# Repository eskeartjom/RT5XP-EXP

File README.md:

# RT5XP-EXP
A input expander for the RetroTINK 5X-Pro

---
## Introduction
The RT5XP-EXP is a purpose build device to extend the input capabilities of the RetroTINK 5X-Pro.

### Input
The Following video signals are supported:

- SCART (RGBS, RGsB, YPbPr)
- Component (YPbPr, RGsB)
- VGA (RGBHV, RGBS, RGsB, YPbPr)

Audio signals can be input as RCA, 3.5mm Jack or SCART and can be selected independently of the video signal.

The sync on scart and component inputs need to be attenuated 75 Ohm signals.
Scart also supports a attenuated CSync signal as the sync input.

The VGA input only supports TTL signals on the sync pins. When using RGsB/YPbPr these need attenuated correctly (which they should be in the first place). VGA also supports TTL CSync on pin 13.

**Input Resolution***: 240p - 1080i

Switching between resolutions is seamless.

### Output

The RT5XP-EXP outputs the signal in RGBS format out of the left scart connector. This signal should be safe to plug into any scart device. The sync signal is a attenuated csync signal.

**Output Resolution***: 240p - 1080i

*Tested on a RetroTINK 5X-Pro and a OSSC

### Display
The big area on the top left shows the line count* of the current input.
The area on the right shows the measured* horizontal and vertical sync signal.
At the bottom the display shows the currenty used and video and audio input.

*The values may not be 100% accurate but close enough.

### Buttons
- P: Cycles thought presets.
- V: Cycles thought different video inputs.
- F: Cycles thought different formats of the current video input.
- A: Cycles thought different audio inputs.

Holding the P button opens a menu. This menu is still WIP.

---
## Hardware
The hardware consists of following things:

- [Main PCB](./Hardware/MainPCB)
- [Display bracked PCB](./Hardware/DisplayPCB)
- [Case](./Hardware/Case)
- [(Optional) SCART PCB](./Hardware/InterconnectPCB)
- [Display](https://www.adafruit.com/product/5394)

---
## Firmware
NOTE: Is still WIP but usable for the basics
- [Firmware](./Firmware)

The firmware is based on a ATmega4809.
I used the Arduino IDE with following libraries:
- [MegaCoreX](https://github.com/MCUdude/MegaCoreX)
- [Adafruit_ST7789](https://github.com/adafruit/Adafruit-ST7735-Library)
- [Adafruit_GFX](https://learn.adafruit.com/adafruit-gfx-graphics-library/overview)

The microcontroller can be flashed via the usb connection.

---
## Misc
Technically the RT5XP-EXP should be support 1080p resolution but i could not test it.

---
## Known issues
On sharp edges there is a purple "color bending". In game this isn't that noticable or might not be noticed at all.

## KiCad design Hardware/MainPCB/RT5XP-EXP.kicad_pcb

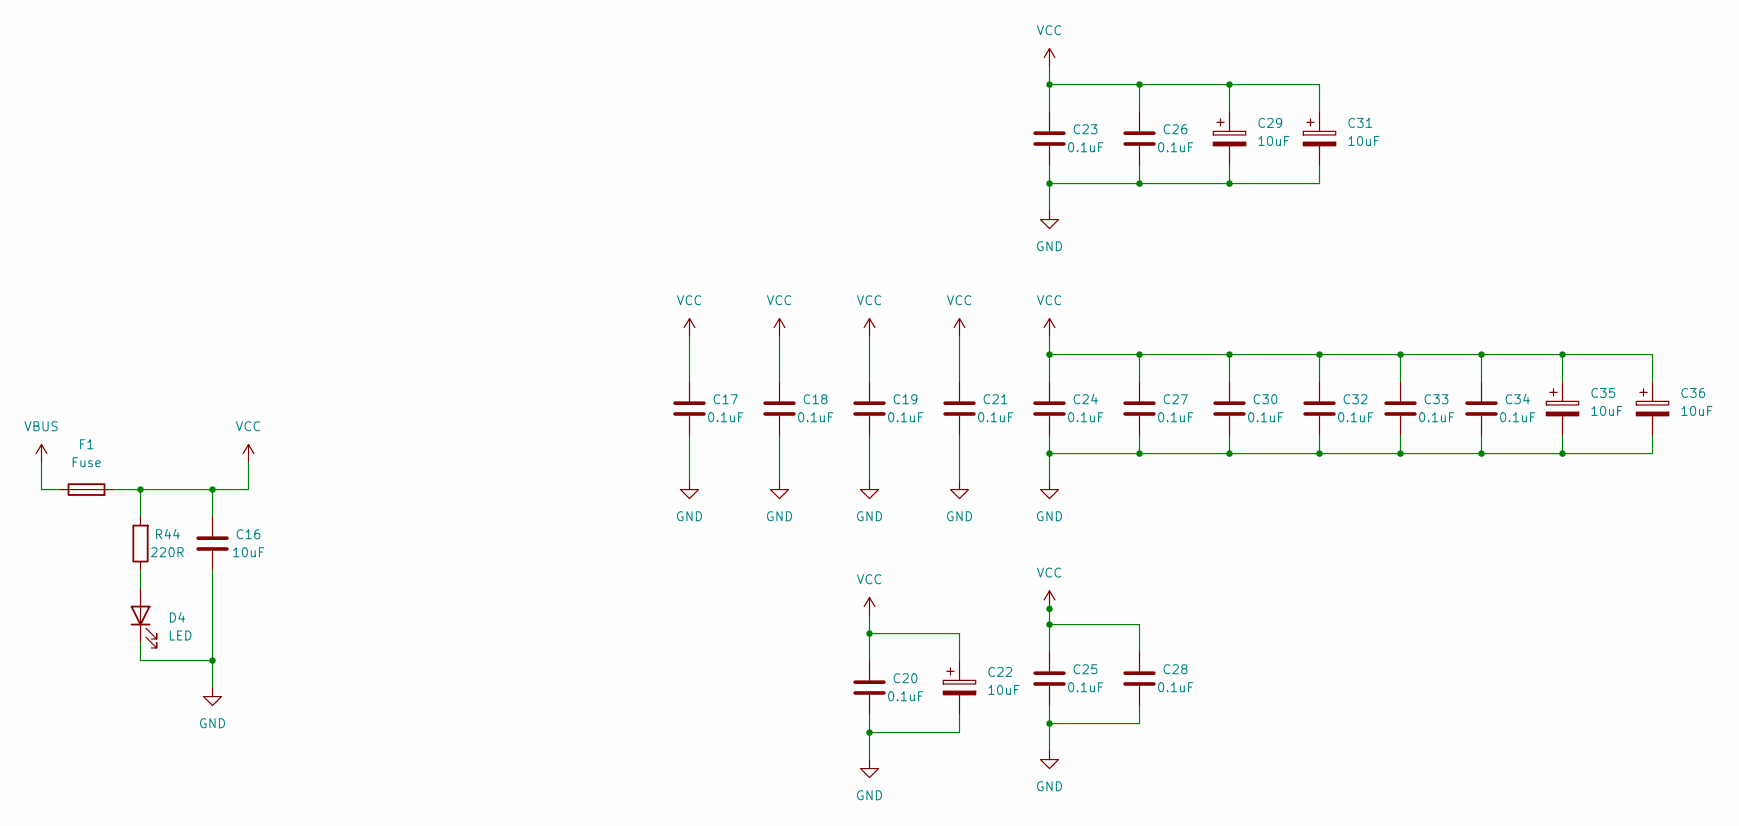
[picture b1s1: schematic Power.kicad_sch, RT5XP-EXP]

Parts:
C16: 10uF; C_0805_2012Metric
C17, C18, C19, C20, C21, C23, C24, C25, C26, C27, C28, C30, C32, C33, C34: 0.1uF; C_0603_1608Metric
C22, C29, C31, C35, C36: 10uF; C_0603_1608Metric
D4: LED; LED_0603_1608Metric
F1: Fuse; Fuse_1210_3225Metric
R44: 220R; R_0603

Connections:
GND: C16.1, C17.1, C18.1, C19.1, C20.1, C21.1, C22.2, C23.1, C24.1, C25.1, C26.1, C27.1, C28.1, C29.2, C30.1, C31.2, C32.1, C33.1, C34.1, C35.2, C36.2, D4.1 (K); also elsewhere on the board
unnamed: D4.2 (A), R44.1
VBUS: F1.1; also elsewhere on the board
VCC: C16.2, C17.2, C18.2, C19.2, C20.2, C21.2, C22.1, C23.2, C24.2, C25.2, C26.2, C27.2, C28.2, C29.1, C30.2, C31.1, C32.2, C33.2, C34.2, C35.1, C36.1, F1.2, R44.2; also elsewhere on the board

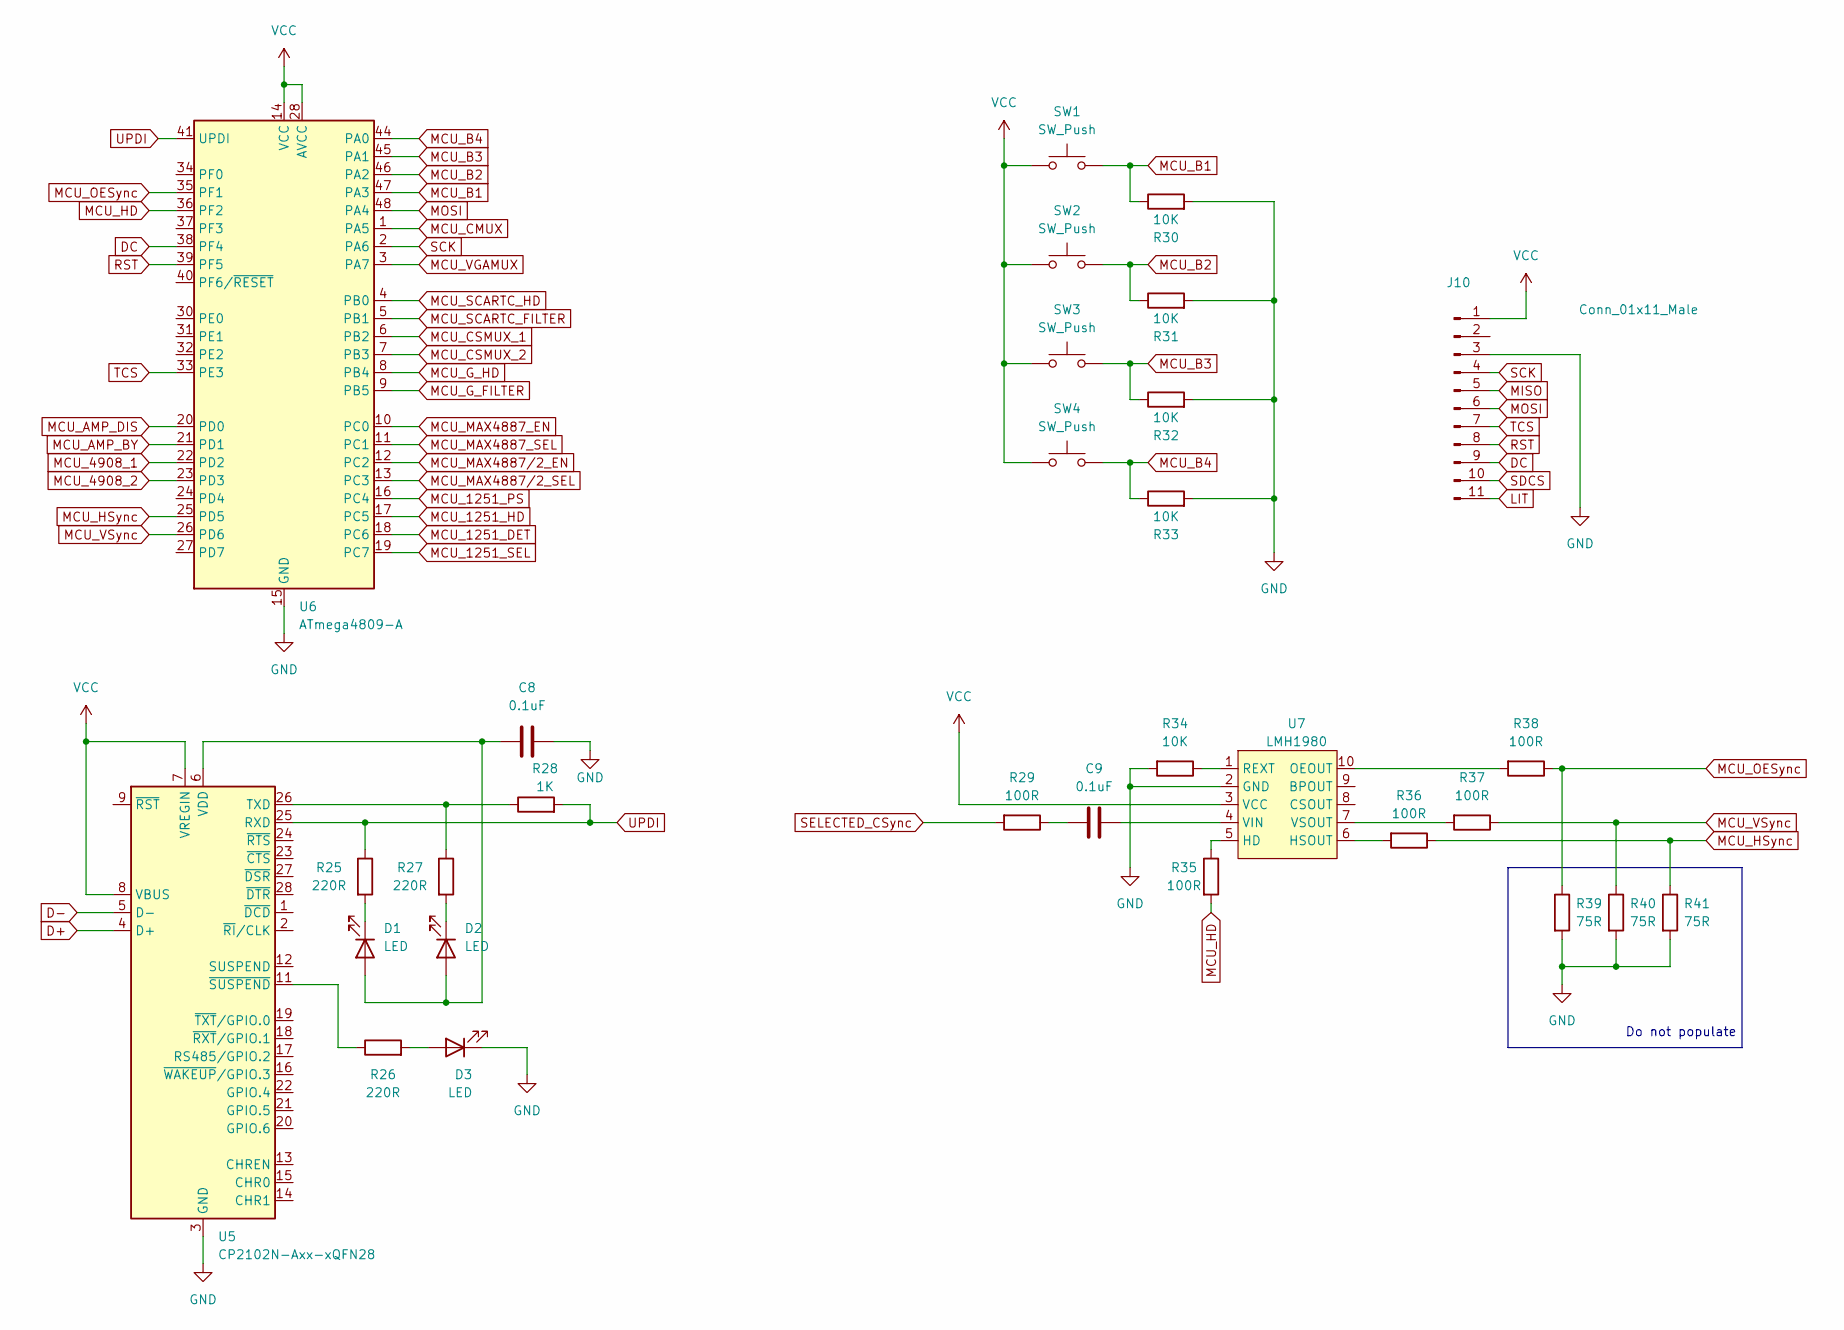
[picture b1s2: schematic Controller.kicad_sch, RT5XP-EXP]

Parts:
C8, C9: 0.1uF; C_0603_1608Metric
D1, D2, D3: LED; LED_0603_1608Metric
J10: Conn_01x11_Male; PinHeader_1x11_P2.54mm_Horizontal
R25, R26, R27: 220R; R_0603
R28: 1K; R_0603
R29, R35, R36, R37, R38: 100R; R_0603
R30, R31, R32, R33, R34: 10K; R_0603
R39, R40, R41: 75R; R_0603
SW1, SW2, SW3, SW4: SW_Push; SW_Tactile_SPST_Angled_PTS645Vx83-2LFS
U5: CP2102N-Axx-xQFN28; QFN-28-1EP_5x5mm_P0.5mm_EP3.35x3.35mm
U6: ATmega4809-A; TQFP-48_7x7mm_P0.5mm
U7: LMH1980; VSSOP-10_3x3mm_P0.5mm

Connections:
D+: U5.4 (D+); also elsewhere on the board
D-: U5.5 (D-); also elsewhere on the board
DC: J10.9, U6.38 (PF4)
GND: C8.1, D3.1 (K), J10.3, R30.2, R31.2, R32.2, R33.2, R34.2, R39.2, R40.2, R41.2, U5.3 (GND), U5.29 (GND), U6.15 (GND), U6.29 (GND), U6.43 (GND), U7.2 (GND); also elsewhere on the board
LIT: J10.11
MCU_1251_DET: U6.18 (PC6); also elsewhere on the board
MCU_1251_HD: U6.17 (PC5); also elsewhere on the board
MCU_1251_PS: U6.16 (PC4); also elsewhere on the board
MCU_1251_SEL: U6.19 (PC7); also elsewhere on the board
MCU_4908_1: U6.22 (PD2); also elsewhere on the board
MCU_4908_2: U6.23 (PD3); also elsewhere on the board
MCU_AMP_BY: U6.21 (PD1); also elsewhere on the board
MCU_AMP_DIS: U6.20 (PD0); also elsewhere on the board
MCU_B1: R30.1, SW1.2, U6.47 (PA3)
MCU_B2: R31.1, SW2.2, U6.46 (PA2)
MCU_B3: R32.1, SW3.2, U6.45 (PA1)
MCU_B4: R33.1, SW4.2, U6.44 (PA0)
MCU_CMUX: U6.1 (PA5); also elsewhere on the board
MCU_CSMUX_1: U6.6 (PB2); also elsewhere on the board
MCU_CSMUX_2: U6.7 (PB3); also elsewhere on the board
MCU_G_FILTER: U6.9 (PB5); also elsewhere on the board
MCU_G_HD: U6.8 (PB4); also elsewhere on the board
MCU_HD: R35.2, U6.36 (PF2)
MCU_HSync: R36.1, R41.1, U6.25 (PD5)
MCU_MAX4887_EN: U6.10 (PC0); also elsewhere on the board
MCU_MAX4887_SEL: U6.11 (PC1); also elsewhere on the board
MCU_MAX4887/2_EN: U6.12 (PC2); also elsewhere on the board
MCU_MAX4887/2_SEL: U6.13 (PC3); also elsewhere on the board
MCU_OESync: R38.1, R39.1, U6.35 (PF1)
MCU_SCARTC_FILTER: U6.5 (PB1); also elsewhere on the board
MCU_SCARTC_HD: U6.4 (PB0); also elsewhere on the board
MCU_VGAMUX: U6.3 (PA7); also elsewhere on the board
MCU_VSync: R37.1, R40.1, U6.26 (PD6)
MISO: J10.5
MOSI: J10.6, U6.48 (PA4)
unnamed: C8.2, D1.2 (A), D2.2 (A), U5.6 (VDD)
unnamed: C9.1, R29.1
unnamed: C9.2, U7.4 (VIN)
unnamed: D1.1 (K), R25.2
unnamed: D2.1 (K), R27.2
unnamed: D3.2 (A), R26.2
unnamed: R26.1, U5.11 (~SUSPEND)
unnamed: R27.1, R28.1, U5.26 (TXD)
unnamed: R34.1, U7.1 (REXT)
unnamed: R35.1, U7.5 (HD)
unnamed: R36.2, U7.6 (HSOUT)
unnamed: R37.2, U7.7 (VSOUT)
unnamed: R38.2, U7.10 (OEOUT)
RST: J10.8, U6.39 (PF5)
SCK: J10.4, U6.2 (PA6)
SDCS: J10.10
SELECTED_CSync: R29.2; also elsewhere on the board
TCS: J10.7, U6.33 (PE3)
UPDI: R25.1, R28.2, U5.25 (RXD), U6.41 (UPDI)
VCC: J10.1, SW1.1, SW2.1, SW3.1, SW4.1, U5.7 (VREGIN), U5.8 (VBUS), U6.14 (VCC), U6.28 (AVCC), U6.42 (VCC), U7.3 (VCC); also elsewhere on the board

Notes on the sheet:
Do not populate

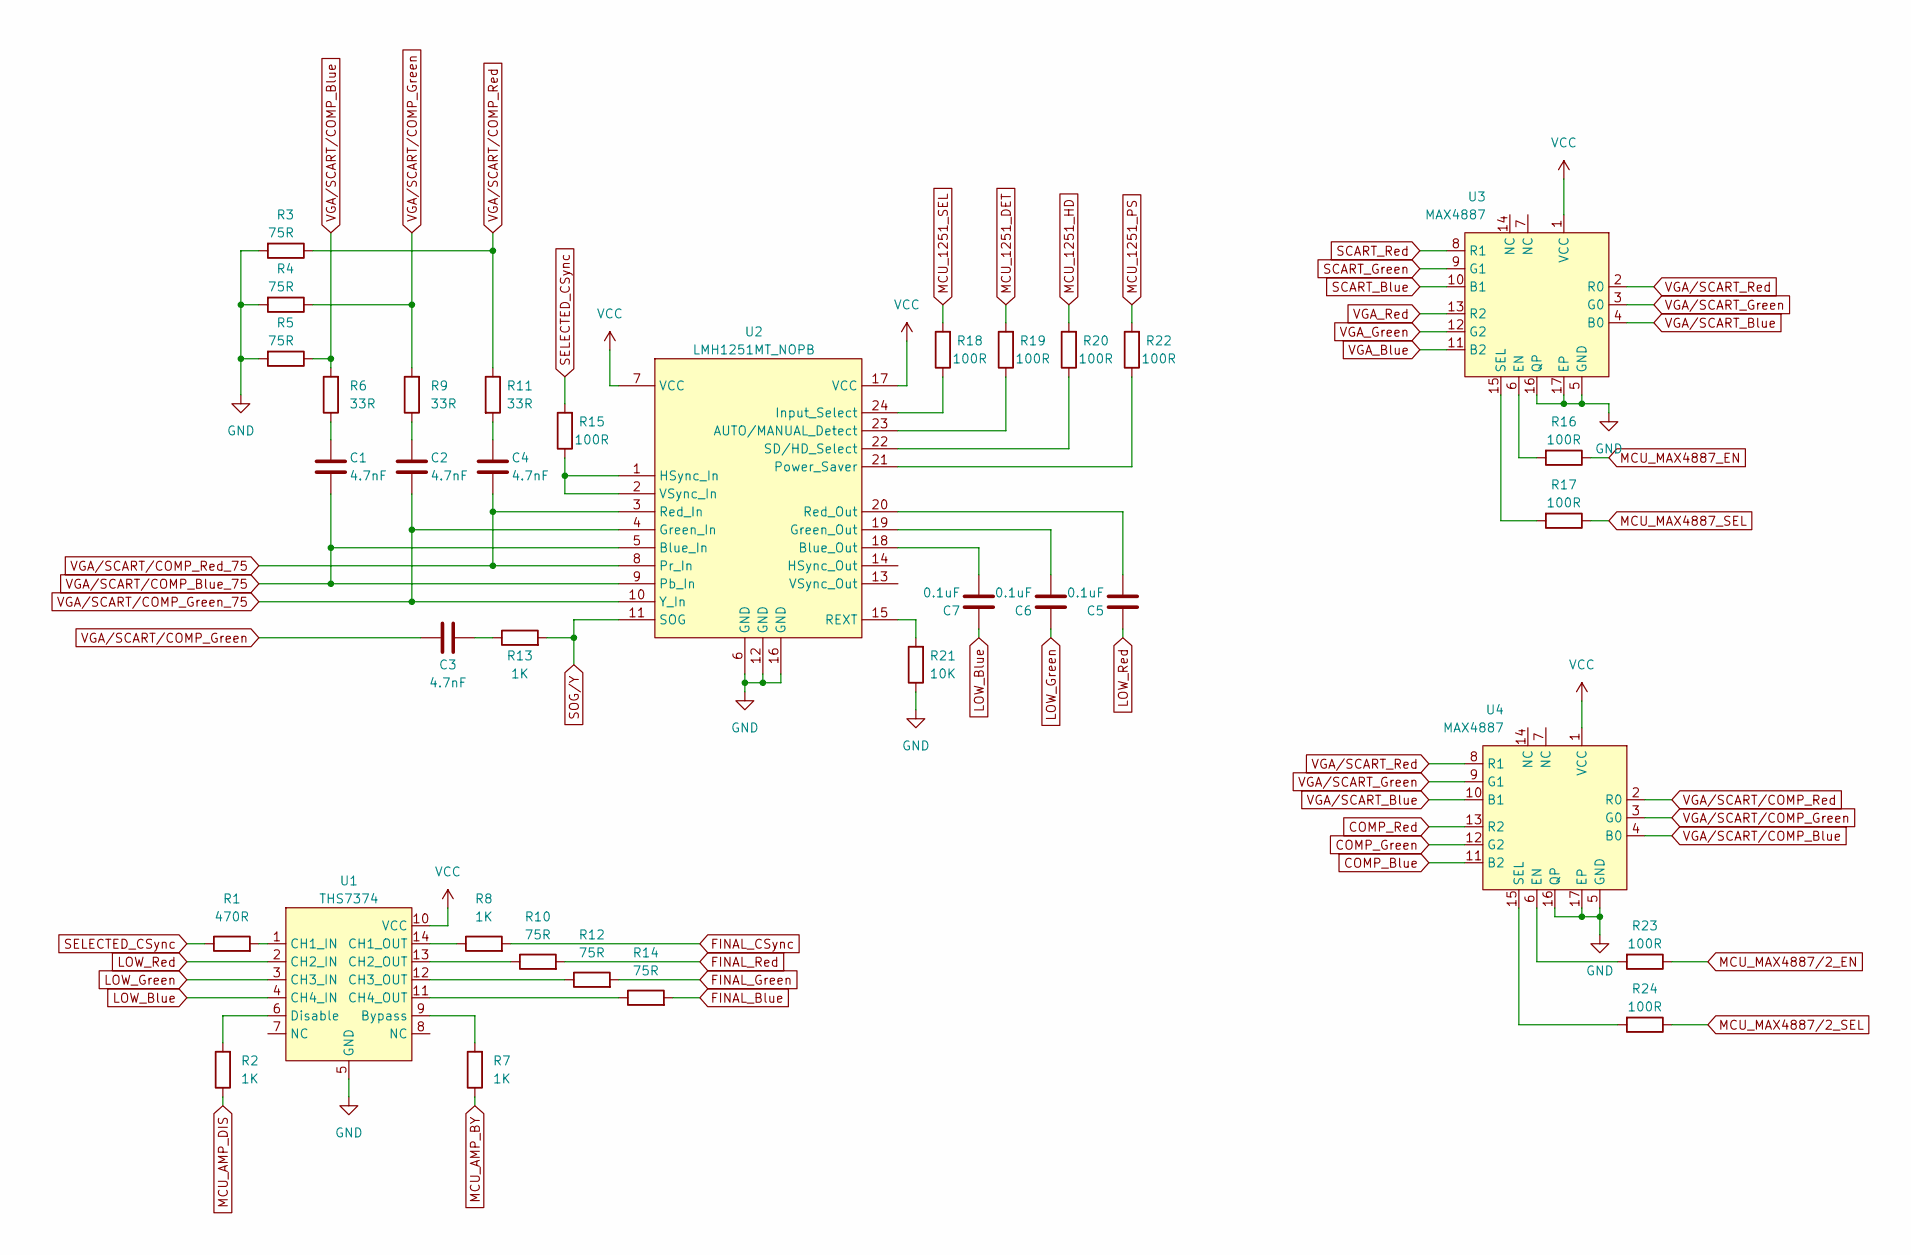
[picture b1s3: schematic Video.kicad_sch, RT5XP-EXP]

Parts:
C1, C2, C3, C4: 4.7nF; C_0603_1608Metric
C5, C6, C7: 0.1uF; C_0603_1608Metric
R1: 470R; R_0603
R2, R7, R8, R13: 1K; R_0603
R3, R4, R5, R10, R12, R14: 75R; R_0603
R6, R9, R11: 33R; R_0603
R15, R16, R17, R18, R19, R20, R22, R23, R24: 100R; R_0603
R21: 10K; R_0603
U1: THS7374; TSSOP-14_4.4x5mm_P0.65mm
U2: LMH1251MT_NOPB; TSSOP-24_4.4x7.8mm_P0.65mm
U3, U4: MAX4887; TQFN-16-1EP_3x3mm_P0.5mm_EP1.23x1.23mm

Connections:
COMP_Blue: U4.11 (B2); also elsewhere on the board
COMP_Green: U4.12 (G2); also elsewhere on the board
COMP_Red: U4.13 (R2); also elsewhere on the board
FINAL_Blue: R14.2; also elsewhere on the board
FINAL_CSync: R8.2; also elsewhere on the board
FINAL_Green: R12.2; also elsewhere on the board
FINAL_Red: R10.2; also elsewhere on the board
GND: R3.2, R4.2, R5.2, R21.1, U1.5 (GND), U2.6 (GND), U2.12 (GND), U2.16 (GND), U3.5 (GND), U3.16 (QP), U3.17 (EP), U4.5 (GND), U4.16 (QP), U4.17 (EP); also elsewhere on the board
LOW_Blue: C7.2, U1.4 (CH4_IN)
LOW_Green: C6.2, U1.3 (CH3_IN)
LOW_Red: C5.2, U1.2 (CH2_IN)
MCU_1251_DET: R19.2; also elsewhere on the board
MCU_1251_HD: R20.2; also elsewhere on the board
MCU_1251_PS: R22.2; also elsewhere on the board
MCU_1251_SEL: R18.2; also elsewhere on the board
MCU_AMP_BY: R7.1; also elsewhere on the board
MCU_AMP_DIS: R2.1; also elsewhere on the board
MCU_MAX4887_EN: R16.1; also elsewhere on the board
MCU_MAX4887_SEL: R17.1; also elsewhere on the board
MCU_MAX4887/2_EN: R23.1; also elsewhere on the board
MCU_MAX4887/2_SEL: R24.1; also elsewhere on the board
unnamed: C1.2, R6.1
unnamed: C2.2, R9.1
unnamed: C3.2, R13.1
unnamed: C4.2, R11.2
unnamed: C5.1, U2.20 (Red_Out)
unnamed: C6.1, U2.19 (Green_Out)
unnamed: C7.1, U2.18 (Blue_Out)
unnamed: R1.2, U1.1 (CH1_IN)
unnamed: R2.2, U1.6 (Disable)
unnamed: R7.2, U1.9 (Bypass)
unnamed: R8.1, U1.14 (CH1_OUT)
unnamed: R10.1, U1.13 (CH2_OUT)
unnamed: R12.1, U1.12 (CH3_OUT)
unnamed: R14.1, U1.11 (CH4_OUT)
unnamed: R15.1, U2.1 (HSync_In), U2.2 (VSync_In)
unnamed: R16.2, U3.6 (EN)
unnamed: R17.2, U3.15 (SEL)
unnamed: R18.1, U2.24 (Input_Select)
unnamed: R19.1, U2.23 (AUTO/MANUAL_Detect)
unnamed: R20.1, U2.22 (SD/HD_Select)
unnamed: R21.2, U2.15 (REXT)
unnamed: R22.1, U2.21 (Power_Saver)
unnamed: R23.2, U4.6 (EN)
unnamed: R24.2, U4.15 (SEL)
SCART_Blue: U3.10 (B1); also elsewhere on the board
SCART_Green: U3.9 (G1); also elsewhere on the board
SCART_Red: U3.8 (R1); also elsewhere on the board
SELECTED_CSync: R1.1, R15.2; also elsewhere on the board
SOG/Y: R13.2, U2.11 (SOG); also elsewhere on the board
VCC: U1.10 (VCC), U2.7 (VCC), U2.17 (VCC), U3.1 (VCC), U4.1 (VCC); also elsewhere on the board
VGA_Blue: U3.11 (B2); also elsewhere on the board
VGA_Green: U3.12 (G2); also elsewhere on the board
VGA_Red: U3.13 (R2); also elsewhere on the board
VGA/SCART_Blue: U3.4 (B0), U4.10 (B1)
VGA/SCART_Green: U3.3 (G0), U4.9 (G1)
VGA/SCART_Red: U3.2 (R0), U4.8 (R1)
VGA/SCART/COMP_Blue: R5.1, R6.2, U4.4 (B0)
VGA/SCART/COMP_Blue_75: C1.1, U2.5 (Blue_In), U2.9 (Pb_In)
VGA/SCART/COMP_Green: C3.1, R4.1, R9.2, U4.3 (G0)
VGA/SCART/COMP_Green_75: C2.1, U2.4 (Green_In), U2.10 (Y_In)
VGA/SCART/COMP_Red: R3.1, R11.1, U4.2 (R0)
VGA/SCART/COMP_Red_75: C4.1, U2.3 (Red_In), U2.8 (Pr_In)

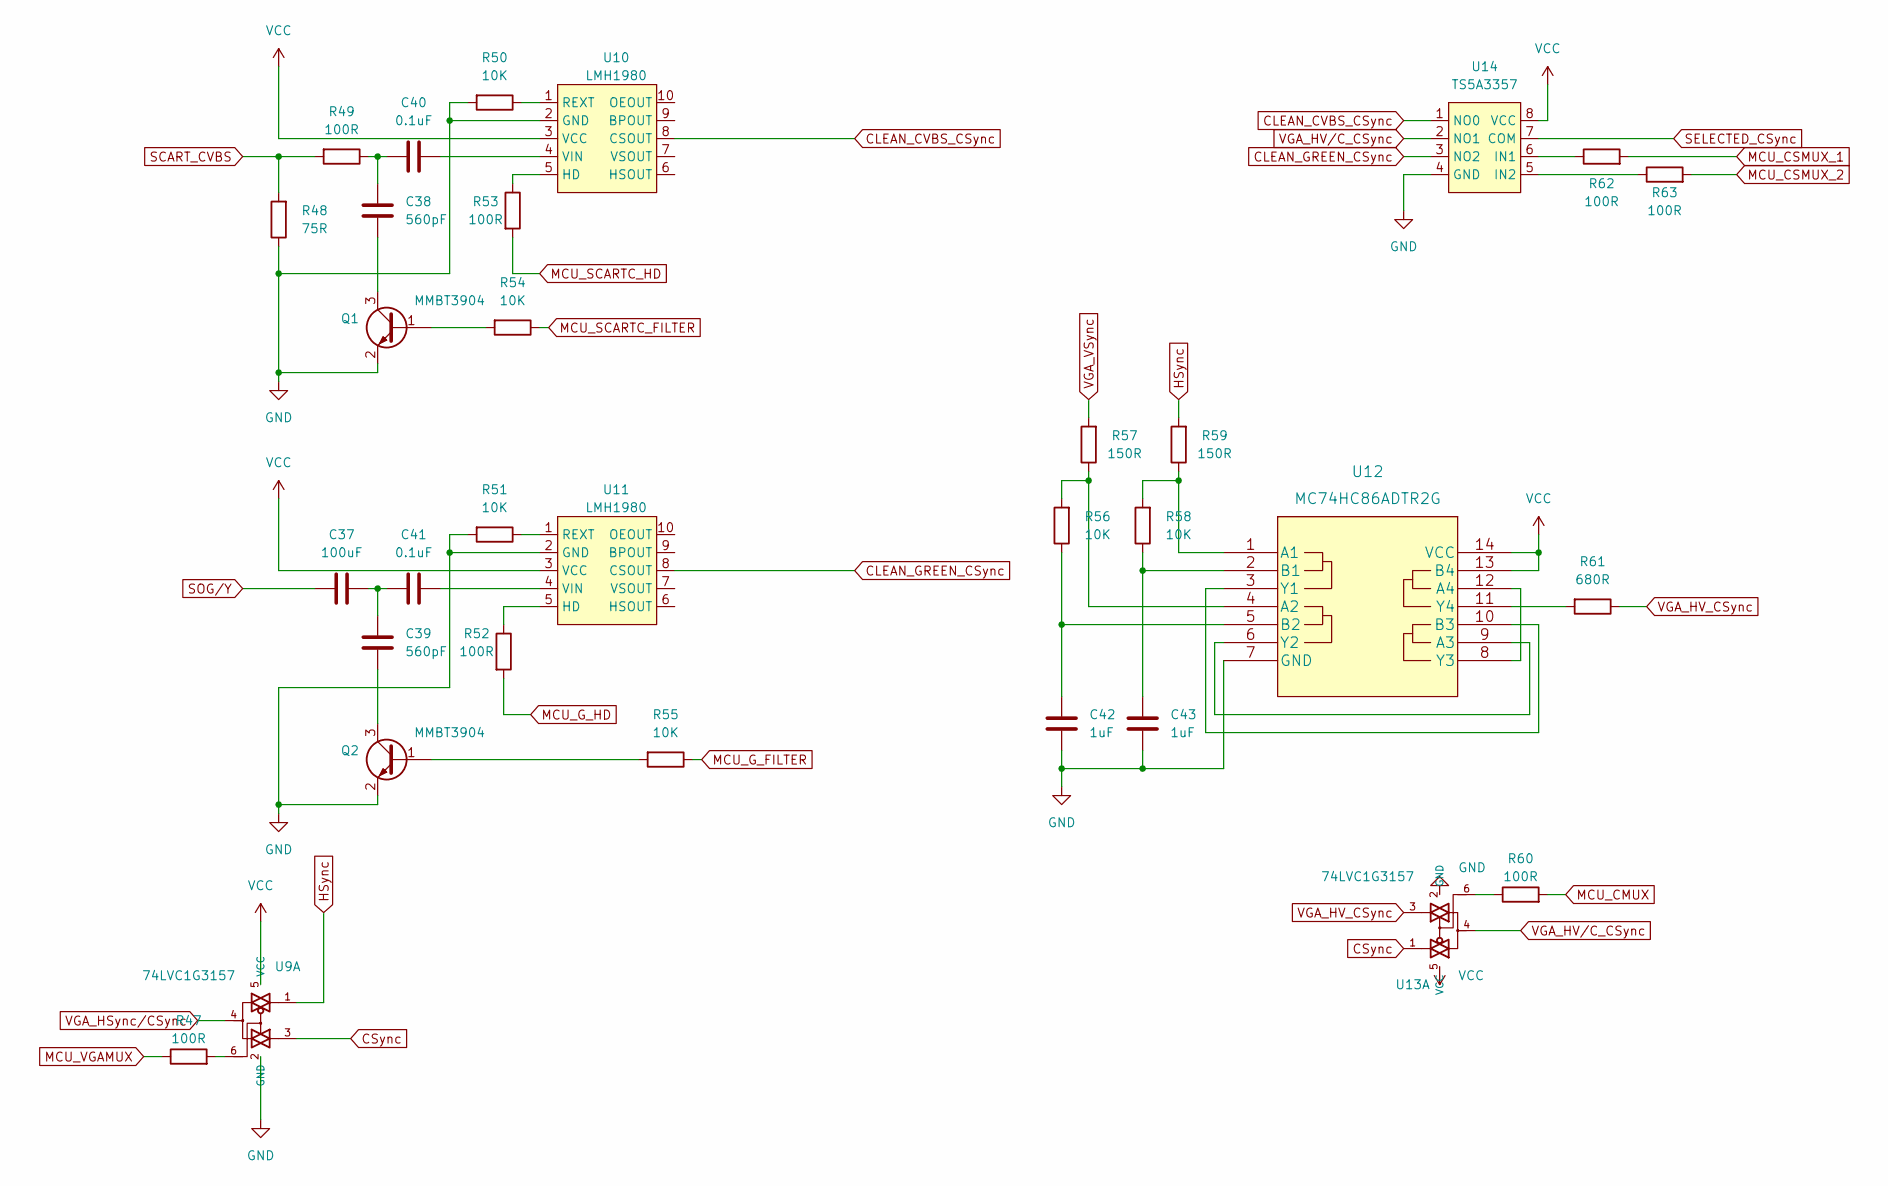
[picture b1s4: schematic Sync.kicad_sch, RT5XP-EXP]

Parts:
C37: 100uF; C_0805_2012Metric
C38, C39: 560pF; C_0603_1608Metric
C40, C41: 0.1uF; C_0603_1608Metric
C42, C43: 1uF; C_0603_1608Metric
Q1, Q2: MMBT3904; SOT-23
R47, R49, R52, R53, R60, R62, R63: 100R; R_0603
R48: 75R; R_0603
R50, R51, R54, R55, R56, R58: 10K; R_0603
R57, R59: 150R; R_0603
R61: 680R; R_0603
U9, U13: 74LVC1G3157; TSOT-23-6
U10, U11: LMH1980; VSSOP-10_3x3mm_P0.5mm
U12: MC74HC86ADTR2G; TSSOP-14_4.4x5mm_P0.65mm
U14: TS5A3357; VSSOP-8_2.3x2mm_P0.5mm

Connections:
CLEAN_CVBS_CSync: U10.8 (CSOUT), U14.1 (NO0)
CLEAN_GREEN_CSync: U11.8 (CSOUT), U14.3 (NO2)
CSync: U9.3, U13.1
GND: C42.1, C43.1, Q1.2 (E), Q2.2 (E), R48.1, R50.2, R51.2, U9.2 (GND), U10.2 (GND), U11.2 (GND), U12.7 (GND), U13.2 (GND), U14.4 (GND); also elsewhere on the board
HSync: R59.2, U9.1
MCU_CMUX: R60.2; also elsewhere on the board
MCU_CSMUX_1: R62.2; also elsewhere on the board
MCU_CSMUX_2: R63.2; also elsewhere on the board
MCU_G_FILTER: R55.1; also elsewhere on the board
MCU_G_HD: R52.2; also elsewhere on the board
MCU_SCARTC_FILTER: R54.1; also elsewhere on the board
MCU_SCARTC_HD: R53.2; also elsewhere on the board
MCU_VGAMUX: R47.1; also elsewhere on the board
unnamed: C37.2, C39.2, C41.1
unnamed: C38.1, Q1.3 (C)
unnamed: C38.2, C40.1, R49.1
unnamed: C39.1, Q2.3 (C)
unnamed: C40.2, U10.4 (VIN)
unnamed: C41.2, U11.4 (VIN)
unnamed: C42.2, R56.1, U12.5 (B2)
unnamed: C43.2, R58.1, U12.2 (B1)
unnamed: Q1.1 (B), R54.2
unnamed: Q2.1 (B), R55.2
unnamed: R47.2, U9.6
unnamed: R50.1, U10.1 (REXT)
unnamed: R51.1, U11.1 (REXT)
unnamed: R52.1, U11.5 (HD)
unnamed: R53.1, U10.5 (HD)
unnamed: R56.2, R57.1, U12.4 (A2)
unnamed: R58.2, R59.1, U12.1 (A1)
unnamed: R60.1, U13.6
unnamed: R61.2, U12.11 (Y4)
unnamed: R62.1, U14.6 (IN1)
unnamed: R63.1, U14.5 (IN2)
unnamed: U12.6 (Y2), U12.9 (A3)
unnamed: U12.3 (Y1), U12.10 (B3)
unnamed: U12.8 (Y3), U12.12 (A4)
SCART_CVBS: R48.2, R49.2; also elsewhere on the board
SELECTED_CSync: U14.7 (COM); also elsewhere on the board
SOG/Y: C37.1; also elsewhere on the board
VCC: U9.5 (VCC), U10.3 (VCC), U11.3 (VCC), U12.13 (B4), U12.14 (VCC), U13.5 (VCC), U14.8 (VCC); also elsewhere on the board
VGA_HSync/CSync: U9.4; also elsewhere on the board
VGA_HV_CSync: R61.1, U13.3
VGA_HV/C_CSync: U13.4, U14.2 (NO1)
VGA_VSync: R57.2; also elsewhere on the board

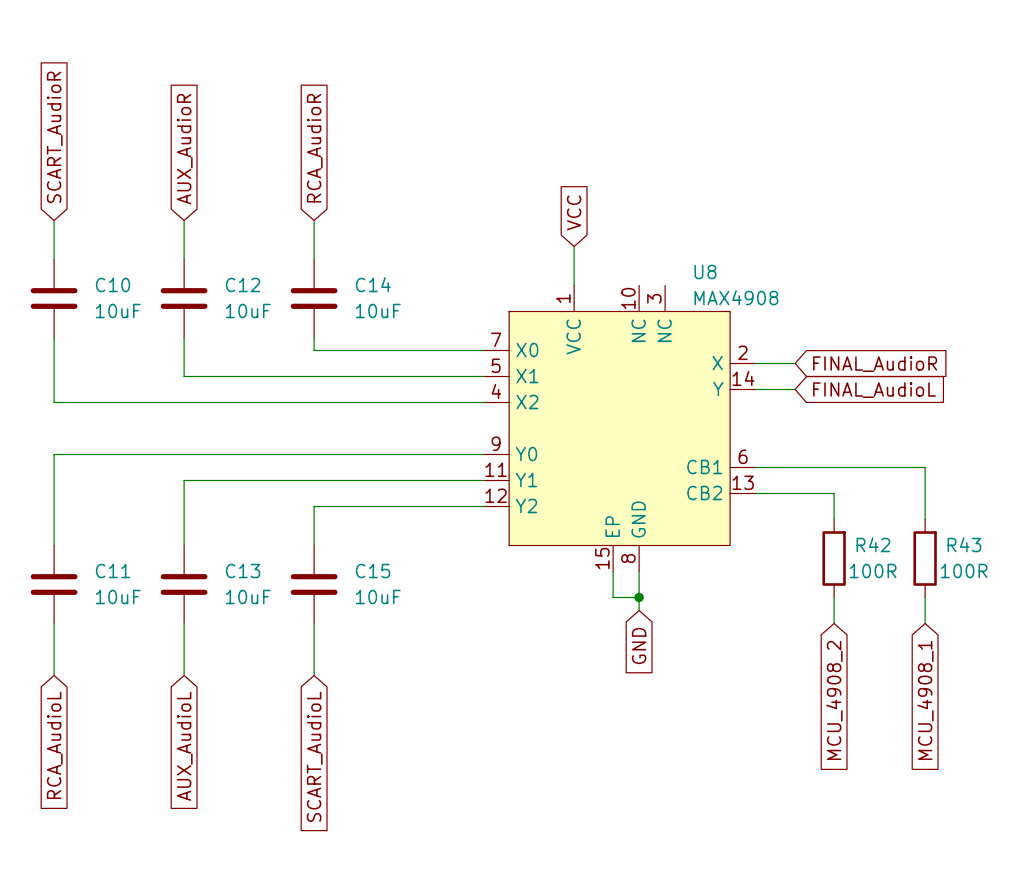
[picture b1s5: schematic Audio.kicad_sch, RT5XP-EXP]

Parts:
C10, C11, C12, C13, C14, C15: 10uF; C_0603_1608Metric
R42, R43: 100R; R_0603
U8: MAX4908; TDFN-14-1EP_3x3mm_P0.4mm_EP1.78x2.35mm

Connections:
AUX_AudioL: C13.1; also elsewhere on the board
AUX_AudioR: C12.2; also elsewhere on the board
FINAL_AudioL: U8.14 (Y); also elsewhere on the board
FINAL_AudioR: U8.2 (X); also elsewhere on the board
GND: U8.8 (GND), U8.15 (EP); also elsewhere on the board
MCU_4908_1: R43.1; also elsewhere on the board
MCU_4908_2: R42.1; also elsewhere on the board
unnamed: C10.1, U8.4 (X2)
unnamed: C11.2, U8.9 (Y0)
unnamed: C12.1, U8.5 (X1)
unnamed: C13.2, U8.11 (Y1)
unnamed: C14.1, U8.7 (X0)
unnamed: C15.2, U8.12 (Y2)
unnamed: R42.2, U8.13 (CB2)
unnamed: R43.2, U8.6 (CB1)
RCA_AudioL: C11.1; also elsewhere on the board
RCA_AudioR: C14.2; also elsewhere on the board
SCART_AudioL: C15.1; also elsewhere on the board
SCART_AudioR: C10.2; also elsewhere on the board
VCC: U8.1 (VCC); also elsewhere on the board

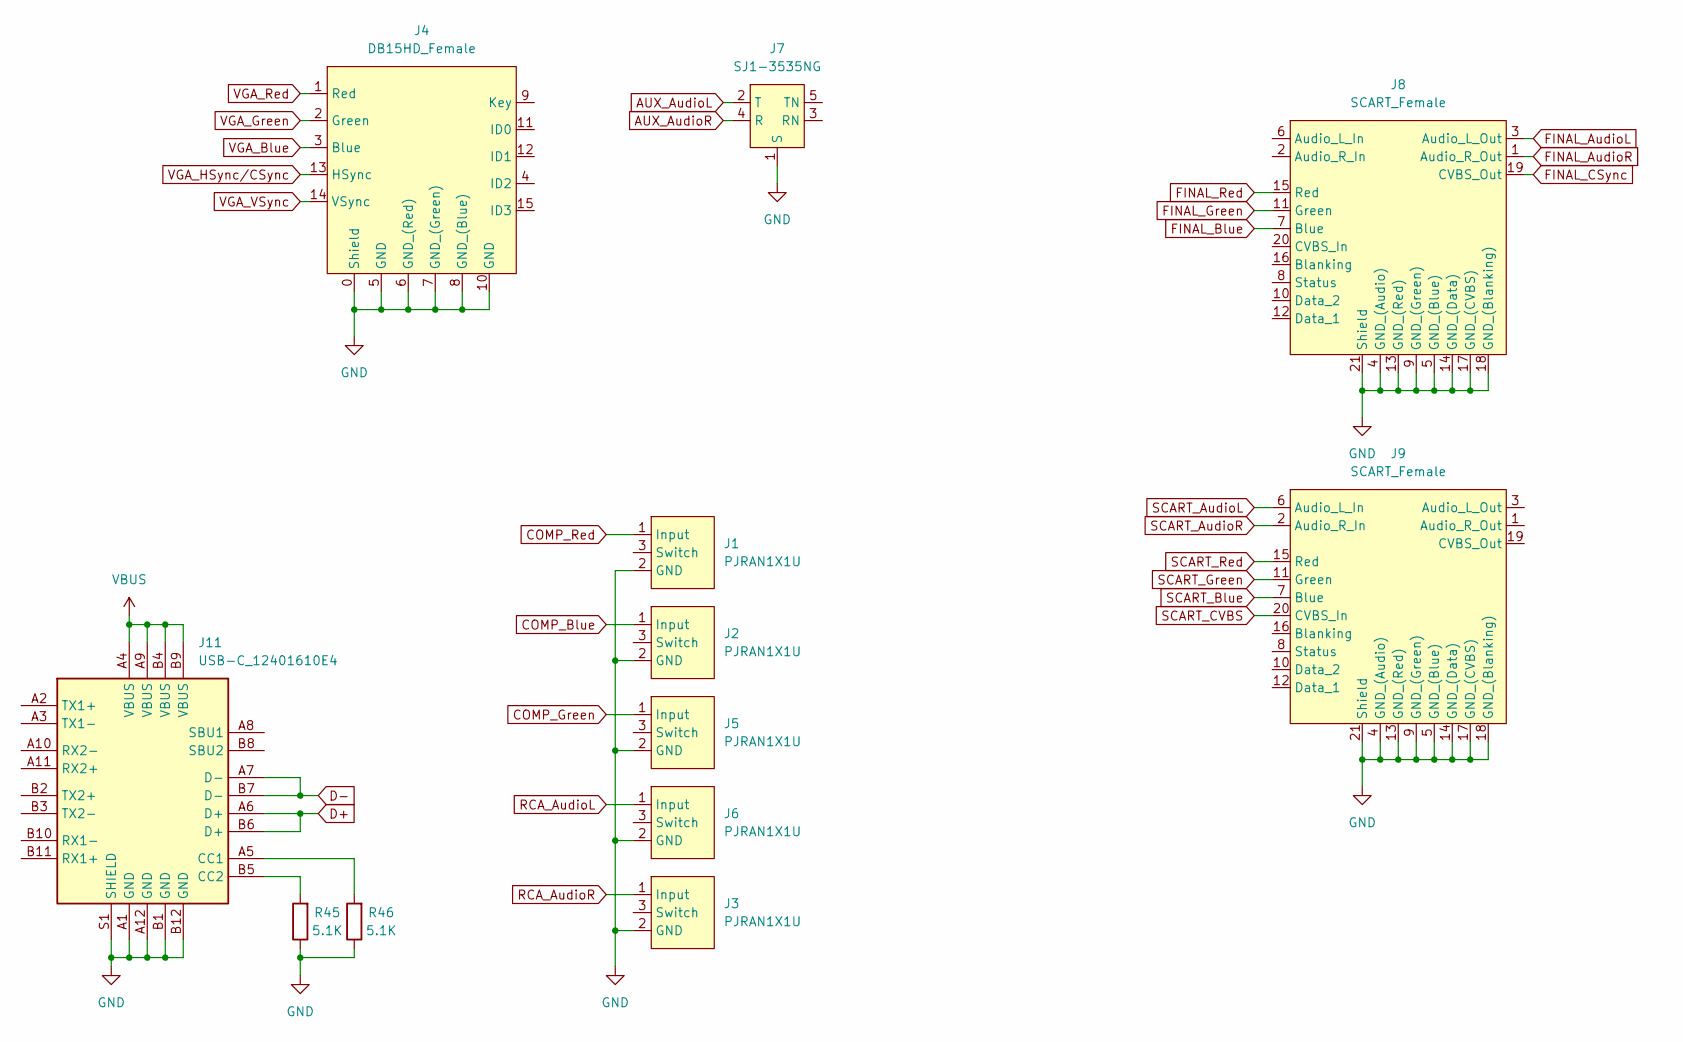
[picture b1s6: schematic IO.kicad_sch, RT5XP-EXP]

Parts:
J1, J2, J3, J5, J6: PJRAN1X1U
J4: DB15HD_Female; 77HDE15SD1CH4RHNVGA
J7: SJ1-3535NG
J8, J9: SCART_Female
J11: USB-C_12401610E4
R45, R46: 5.1K; R_0603

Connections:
AUX_AudioL: J7.2 (T); also elsewhere on the board
AUX_AudioR: J7.4 (R); also elsewhere on the board
COMP_Blue: J2.1 (Input); also elsewhere on the board
COMP_Green: J5.1 (Input); also elsewhere on the board
COMP_Red: J1.1 (Input); also elsewhere on the board
D+: J11.A6 (D+), J11.B6 (D+); also elsewhere on the board
D-: J11.A7 (D-), J11.B7 (D-); also elsewhere on the board
FINAL_AudioL: J8.3 (Audio_L_Out); also elsewhere on the board
FINAL_AudioR: J8.1 (Audio_R_Out); also elsewhere on the board
FINAL_Blue: J8.7 (Blue); also elsewhere on the board
FINAL_CSync: J8.19 (CVBS_Out); also elsewhere on the board
FINAL_Green: J8.11 (Green); also elsewhere on the board
FINAL_Red: J8.15 (Red); also elsewhere on the board
GND: J1.2 (GND), J2.2 (GND), J3.2 (GND), J4.0 (Shield), J4.5 (GND), J4.6 (GND_(Red)), J4.7 (GND_(Green)), J4.8 (GND_(Blue)), J4.10 (GND), J5.2 (GND), J6.2 (GND), J7.1 (S), J8.4 (GND_(Audio)), J8.5 (GND_(Blue)), J8.9 (GND_(Green)), J8.13 (GND_(Red)), J8.14 (GND_(Data)), J8.17 (GND_(CVBS)), J8.18 (GND_(Blanking)), J8.21 (Shield), J9.4 (GND_(Audio)), J9.5 (GND_(Blue)), J9.9 (GND_(Green)), J9.13 (GND_(Red)), J9.14 (GND_(Data)), J9.17 (GND_(CVBS)), J9.18 (GND_(Blanking)), J9.21 (Shield), J11.A1 (GND), J11.A12 (GND), J11.B1 (GND), J11.B12 (GND), J11.S1 (SHIELD), R45.1, R46.1; also elsewhere on the board
unnamed: J11.A5 (CC1), R46.2
unnamed: J11.B5 (CC2), R45.2
RCA_AudioL: J6.1 (Input); also elsewhere on the board
RCA_AudioR: J3.1 (Input); also elsewhere on the board
SCART_AudioL: J9.6 (Audio_L_In); also elsewhere on the board
SCART_AudioR: J9.2 (Audio_R_In); also elsewhere on the board
SCART_Blue: J9.7 (Blue); also elsewhere on the board
SCART_CVBS: J9.20 (CVBS_In); also elsewhere on the board
SCART_Green: J9.11 (Green); also elsewhere on the board
SCART_Red: J9.15 (Red); also elsewhere on the board
VBUS: J11.A4 (VBUS), J11.A9 (VBUS), J11.B4 (VBUS), J11.B9 (VBUS); also elsewhere on the board
VGA_Blue: J4.3 (Blue); also elsewhere on the board
VGA_Green: J4.2 (Green); also elsewhere on the board
VGA_HSync/CSync: J4.13 (HSync); also elsewhere on the board
VGA_Red: J4.1 (Red); also elsewhere on the board
VGA_VSync: J4.14 (VSync); also elsewhere on the board

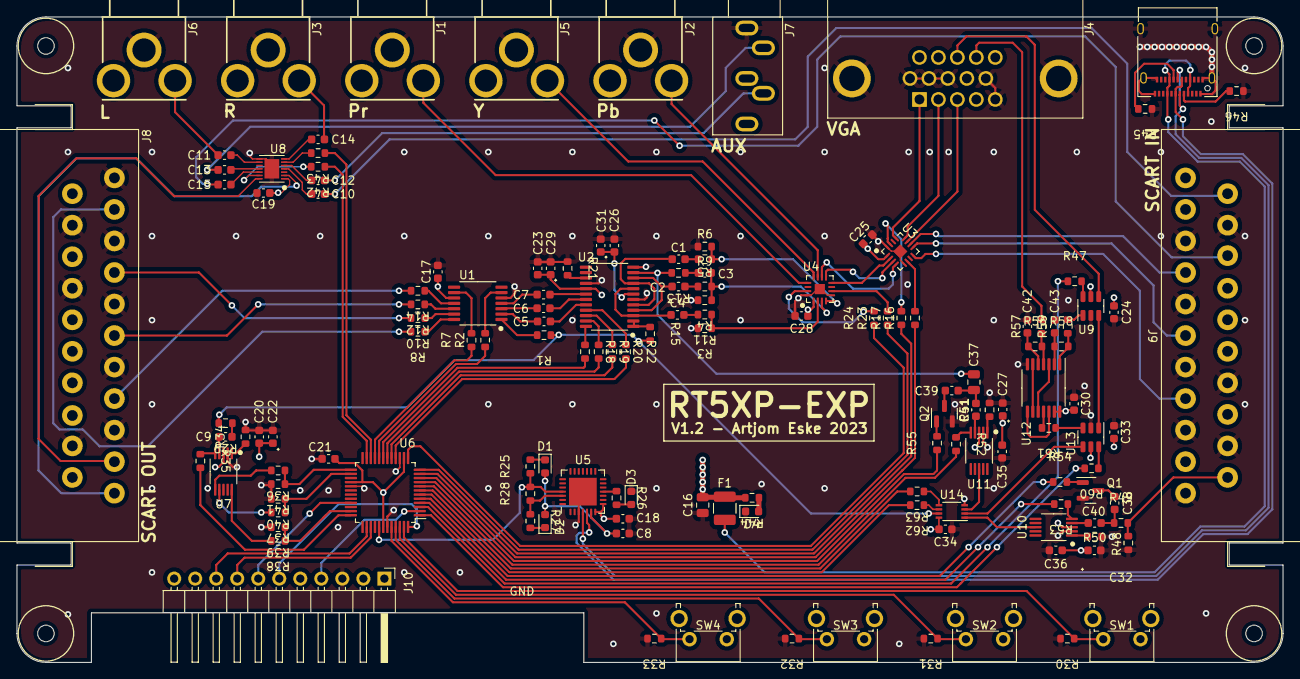
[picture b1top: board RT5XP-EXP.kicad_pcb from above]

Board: 4 copper layers, 153.0 x 78.0 mm, 142 parts (0 on the bottom side), 155 nets.

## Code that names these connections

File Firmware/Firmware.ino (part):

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// Version 1.1 - Min HW: 1.3

/**************************************************************************
#define PIN_PA0 0 RX_CP2102
#define PIN_PA1 1 TX_CP2102
#define PIN_PA2 2
#define PIN_PA3 3
#define PIN_PA4 4 MOSI_Display
#define PIN_PA5 5
#define PIN_PA6 6 SCK_Display
#define PIN_PA7 7
#define PIN_PB0 8
#define PIN_PB1 9
#define PIN_PB2 10
#define PIN_PB3 11
#define PIN_PB4 12
#define PIN_PB5 13
#define PIN_PC0 14
#define PIN_PC1 15
#define PIN_PC2 16
#define PIN_PC3 17
#define PIN_PC4 18
#define PIN_PC5 19
#define PIN_PC6 20
#define PIN_PC7 21
#define PIN_PD0 22
#define PIN_PD1 23
#define PIN_PD2 24
#define PIN_PD3 25
#define PIN_PD4 26
#define PIN_PD5 27 HSync
#define PIN_PD6 28 VSync
#define PIN_PD7 29
#define PIN_PE0 30
#define PIN_PE1 31
#define PIN_PE2 32
#define PIN_PE3 33 TCS_Display
#define PIN_PF0 34
#define PIN_PF1 35 Odd/Even
#define PIN_PF2 36
#define PIN_PF3 37
#define PIN_PF4 38 DC_Display
#define PIN_PF5 39 RST_Display
#define PIN_PF6 40 CP2021
**************************************************************************/

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#define SL_COLOR 0xC409
#define FONT_W 6
#define FONT_H 8
#define HS_TEXT "HSync:"
#define VS_TEXT "VSync:"
#define VD_TEXT "Video: "
#define AD_TEXT "Audio: "
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// HW Timer

void initEventSystem(void) {
	EVSYS.CHANNEL2 = EVSYS_GENERATOR_PORT1_PIN5_gc;  // connect Pin 'PD5' to channel 2
	EVSYS.USERTCB0 = EVSYS_CHANNEL_CHANNEL2_gc;      // connect 'generator 'PD5' with user 'TCB0' via channel 2

	EVSYS.CHANNEL3 = EVSYS_GENERATOR_PORT1_PIN6_gc;
	EVSYS.USERTCB1 = EVSYS_CHANNEL_CHANNEL3_gc;
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
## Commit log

2023-08-26 Added hardware and firmware
2023-08-26 Create LICENSE
2023-09-13 Fixed color bending issue; Added diagnostics

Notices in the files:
Firmware/Firmware.ino:
(c) 2013 Artjom Eske
This code is licensed under MIT license (see LICENSE.txt for details)
